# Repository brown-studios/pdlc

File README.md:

# PDLC driver

Drives [polymer dispersed liquid crystal (PDLC) film](https://en.wikipedia.org/wiki/Smart_glass#Polymer-dispersed_liquid-crystal_devices) from a 12 V DC nominal power supply.

PDLC film is opaque when turned off and becomes clear when turned on.  For example, you can apply it to a window to replace a privacy curtain or to create a diffuse surface for a projection screen on demand.

## Features

Here are some of the features of this PDLC driver board:

- Runs on a 12 V DC battery or power supply at a maximum of 16 V DC
- Drives approximately 4 square meters of PDLC film depending on its electrical characteristics with 15 W of power at 60 V AC peak-to-peak nominal
- Shuts off automatically to protect the battery when the supply voltage falls below 10.6 V DC and resumes operation at 11.5 V
- Includes several forms of circuit protection for the supply and the film
- Detach the terminal blocks from the device for easier wiring
- Optional external I/O functions
  - Connect the mode input to an external momentary push button or a normally open switch to control the state of the film from a convenient location
  - Connect the output enable control signal to a switch to control whether the PDLC film is operable (e.g. can be wired to a door sensor to prevent activation of the film when the door is opened)
  - Connect the auxiliary load output to control another device in tandem with the PDLC film, supports low-side switching of a 200 mA load at up to 20 V maximum (e.g. can be wired to an external indicator)
  - Connect an external I2C controller to control the driver programmatically
  - Connect your own accessories to the expansion port

Please refer to the [design and errata](./hardware/v2/design-and-errata.md) for technical details and schematics.

## Usage

If you have not yet [installed](#installation) and [setup](#setup) the device, do that first then proceed with usage.

How you use the PDLC driver depends on how you have configured it and integrated it with other systems.

By default, the PDLC film toggles on and off when you press the `MODE` button on the device.  When the film is on, it will turn clear, and when it is off, it will become diffuse and provide privacy.  The transition usually happens in less than a second but the film may take longer to change depending on your configuration settings or when the window is very cold.

You can connect an external push button or switch to change the state of the film from a more convenient location. If you have one, use that actuator instead of the `MODE` button.

As a safety feature, the film will not turn on unless the output enable control signal is active, so you may also need to perform another action to enable the film (such as closing the door if you have connected the output enable to a door switch).

You can connect an auxiliary load to the PDLC driver and configure it such that it turns on or off based on the state of the PDLC film automatically. So turning on or off the PDLC film can have additional effects depending on how you have wired things up.

Also, you can programmatically control the PDLC driver using I2C and adjust many internal settings and use advanced functionality such as dimming.  You'll need to write code for this or use an integration that someone else has made.

The `POWER` indicator illuminates for 10 seconds after you supply power to the device then turns off.

The `STATUS` indicator color indicates the status of the PDLC driver during normal operation.  The indicator may blink a certain number of times, pause, then repeat to encode information about a problem.  This table explains the significance of the patterns.

| Status color | Pattern    | Meaning |
| ------------ | ---------- | ------- |
| GREEN        | steady     | The PDLC driver is providing power to the PDLC film. |
| YELLOW       | steady     | The PDLC driver is turning on and verifying its operation. |
| AMBER        | 1 blink    | The PDLC driver was commanded to turn the film on but the output enable control signal is inactive so the driver is not providing power to the PDLC film. |
| RED          | 1 blinks   | HV_TIMEOUT: Boost converter did not report power good within the expected time after being enabled. |
| RED          | 2 blinks   | HV_FAULT: Boost converter reported power good then subsequently reported not power good. |
| RED          | 3 blinks   | OUTPUT_TIMEOUT: Buck converter did not report power good within the expected time after being enabled. |
| RED          | 4 blinks   | OUTPUT_FAULT: Buck converter reported power good then subsequently reported not power good. |
| RED          | 5 blinks   | DRIVER: An error occurred in the driver. |

Refer to the [setup](#setup) guide for information about how this indicator is used while configuring settings.

## Troubleshooting

When the PDLC film doesn't turn on when you think it should...

- Try turning the film off then on again and look at the `STATUS` indicator for clues.  Perhaps the output is not enabled.
- Disconnect and reconnect power to the device.  The `POWER` indicator should illuminate briefly once power is connected.
- Ensure that your power supply or battery is supplying at least 11.5 V to the device.
- Check that the settings are compatible with your installation.
- If under programmatic control, disconnect the external I2C controller, factory reset the settings, and try again using the built-in buttons to confirm basic operation.
- Check all wiring connections, fuses, and external control inputs.

When the PDLC film doesn't turn off when you think it should...

- Check that the settings are compatible with your installation.
- Check all wiring connections, fuses, and external control inputs.

## Setup

If you have not yet [installed](#installation) the device, do that first then proceed with setup.

Start by locating the `MODE` button, `SET` button, and `STATUS` indicator on the PDLC driver [as shown during installation](#installation).  Here's how to navigate the setting menus.

1. If you have connected an external switch to the `CONTROL CTRL_MODE_IN` terminal, then turn the switch off before changing settings to prevent interference with the `MODE` push button of the PDLC driver.
2. Press the `SET` button to turn off the PDLC film and enter the first setting menu.
3. Look at the `STATUS` indicator.
  - The color of the status indicator tells you which setting menu is active.
  - The indicator will blink a certain number of times, pause, then repeat.  The number of blinks tells you which option of the setting menu is selected.
4. Press the `MODE` button to advance to the next option.  The indicator will begin blinking a different number of times corresponding to the newly selected option.
5. Press the `SET` button to advance to the next setting menu and the color of the `STATUS` indicator will change.  Repeat from step 3 to continue changing settings.
6. Once you have configured the last option, the `STATUS` indicator will turn off and return to normal function.  Similarly, if you wait 30 seconds without interacting with the setting menu the device will exit the setting menu automatically.

> ![IMPORTANT]
> To reset the device to factory default settings, press and hold the `SET` button for 10 seconds until the indicator cycles through a rainbow pattern to confirm.

| Menu color | Option blinks  | Behavior |
| ---------- | -------------- | -------- |
| BLUE       | 1 (default)    | The PDLC film toggles on and off each time `MODE` is pressed. Use this option when you connect a momentary push button to the `CONTROL CTRL_MODE_IN` terminal. |
| BLUE       | 2              | The PDLC film turns on while `MODE` is pressed and turns off while `MODE` is released. Use this option when you connect a normally open switch to the `CONTROL CTRL_MODE_IN` terminal. |
| BLUE       | 3              | The PDLC film state is always on whenever the output enable control signal is active. Use this option when you are controlling the PDLC driver programmatically and do not want the `MODE` button to interfere. |
| BLUE       | 4              | The PDLC film state is always off. Use this option when you are controlling the PDLC driver programmatically and do not want the `MODE` button to interfere. |
| MAGENTA    | 1 (default)    | The PDLC film transitions from opaque to clear as quickly as possible. |
| MAGENTA    | 2              | The PDLC film transitions from opaque to clear gradually over a duration of about 0.5 seconds. |
| MAGENTA    | 3              | The PDLC film transitions from opaque to clear gradually over a duration of about 1 second. |
| MAGENTA    | 4              | The PDLC film transitions from opaque to clear gradually over a duration of about 2 seconds. |
| CYAN       | 1 (default)    | The auxiliary load output turns on when the PDLC film is on and turns off otherwise (same state). |
| CYAN       | 2              | The auxiliary load output turns off when the PDLC film is on and turns on otherwise (opposite state). |
| CYAN       | 3              | The auxiliary load output is always on. |
| CYAN       | 4              | The auxiliary load output is always off. |

## Installation

To begin installing and using your PDLC driver, locate these parts of your device:

| Part                     | Function |
| ------------------------ | -------- |
| `POWER` terminal block   | Connect the power supply and the PDLC film as described in the [wiring guide](#wiring). |
| `CONTROL` terminal block | Connect the control inputs and outputs as described in the [wiring guide](#wiring). |
| `POWER` indicator        | Indicates that the device has power.  Turns off automatically after a few seconds of inactivity. |
| `STATUS` indicator       | Indicates the status of the device and provides visual feedback while you configure settings. |
| `MODE` button            | By default, toggles the PDLC panel on/off.  Can be configured to behave in other ways. |
| `SET` button             | Configures device settings. |
| `EN` solder jumper       | Solder closed to force the output enable control signal to be always active. |
| `EXT I2C` connector      | Allows an external device to control the PDLC driver programmatically using a [QWIIC-compatible](https://www.sparkfun.com/qwiic) I2C interface with galvanic isolation. Additional I2C devices can also be connected in a daisy-chain. |
| `EXPANSION` header       | Connect your own accessories to this port to take advantage of otherwise unused microcontroller pins. |

### Identify the terminals

Remove both terminal blocks from the device by grasping the sides of a block and gently pulling the block out from its socket.  Do not tug on any wires that you may have already connected to the terminal blocks because pulling on the wires could damage them.

Identify the terminals of each terminal block.  You may use the silkscreen legend on the back side of the PCB as a guide, taking care to note the orientation of the connector when it is plugged in.  The following sections will describe these connections in more detail.

We recommend crimping [electric wire ferrules](https://en.wikipedia.org/wiki/Electric_wire_ferrule) onto the wires before screwing them into place to make your connections more secure.  Only moderate screw tension is required.

| Block    | Terminal | Name         | Function |
| -------- | -------- | ------------ | -------- |
| POWER    | 1        | GND          | Power supply input with negative polarity. |
| POWER    | 2        | 12V_IN       | Power supply input with positive polarity. |
| POWER    | 3        | PDLC_OUT_A   | PDLC panel AC output A. |
| POWER    | 4        | PDLC_OUT_B   | PDLC panel AC output B. |
| CONTROL  | 1        | GND          | Connected to `POWER GND`. |
| CONTROL  | 2        | CTRL_EN_IN   | Output enable switch input.  Active when connected to `GND`. |
| CONTROL  | 3        | CTRL_MODE_IN | Mode switch input.  Active when connected to `GND`. |
| CONTROL  | 4        | GND          | Connected to `POWER GND`. |
| CONTROL  | 5        | LOAD_OUT     | Auxiliary load output. |
| CONTROL  | 6        | 12V_OUT      | Connected to the 12V rail downstream of the internal fuse circuit protection.  DO NOT CONNECT TO POWER SUPPLY. |

### Connect the power supply (required)

You must connect the driver to a suitable 12 V DC nominal power supply.  It must be capable of supplying at least 2 amps of current and have suitable overcurrent protection such as a fuse or circuit breaker.

Use 20 AWG (0.5 mm^2) wire or larger to make the connections.

Connect the `POWER GND` terminal to the negative (ground) side of your power supply.

Connect the `POWER 12V_IN` terminal to a 3 A fuse or circuit breaker attached to the positive side of your power supply.

### Connect the PDLC film (required)

Use 22 AWG (0.3 mm^2) wire or larger to make the connections, preferably double-insulated.

Connect the `POWER PDLC_OUT_A` and `POWER PDLC_OUT_B` terminals to the PDLC film.  Either terminal can be connected to the PDLC film in either orientation because the film uses AC and there is no distinct polarity.

> ![WARNING]
> The PDLC power wires carry high voltage similar to domestic electrical wiring systems.  They can deliver a small electric shock that could be harmful to people so please ensure that these wires are adequately insulated and without exposed connections that could accidentally be touched!
>
> If the connection passes through a contact surface that might intermittently be exposed to people or to the environment (such as through a sliding door contact plate) install a safety device to deactivate the output enable control signal (such as a door switch) when those contacts may be exposed to reduce the risk of harm.

### Connect the output enable control signal (required)

The PDLC driver only provides power to the PDLC film when the output enable control signal is connected to ground.  This mechanism can be used to implement safety features to automatically disable the film when it is not safe to operate (such as when the contacts may be exposed as described in the previous section) or to remotely enable or disable the film using other devices.

> ![IMPORTANT]
> By default, the output enable control signal is not connected to anything (it is inactive) and the driver will not operate the PDLC film.  So for the PDLC film to operate, you must make a connection to activate the output enable control signal.

Here are three ways to do activate the output enable control signal:

- Connect a switch between the `CONTROL CTRL_EN_IN` and `CONTROL GND` terminals that is closed whenever it is safe to operate the PDLC film and open otherwise.  Alternatively, you may use a relay, transistor, or an optocoupler to drive the signal low (connect it to ground).
- Connect a short piece of wire with bare ends between the `CONTROL CTRL_EN_IN` and `CONTROL GND` terminals to ensure that the signal is always active when there is no reason to disable the film.
- Solder the `EN` jumper closed to bypass the `CONTROL` terminal block and ensure that the signal is always active when there is no reason to disable the film.

### Connect an external mode actuator (optional)

Optionally, you can connect an external actuator to control the mode of the PDLC driver from a more convenient location such as when you install the PDLC driver inside of a cabinet.

Choose one of following actuators and make note of its corresponding `MODE` behavior.

| Actuator type              | Behavior | Description |
| -------------------------- | -------- | ----------- |
| SPST momentary push button | Toggle   | Toggle the film on or off each time the button is pressed. |
| SPST normally open switch  | On / Off | Turn the film on when the switch is closed and off when the switch is open. |

Use 24 AWG (0.2 mm^2) wire or larger to make the connections.

Connect the actuator to the `CONTROL CTRL_MODE_IN` and `CONTROL GND` terminals such that the circuit is closed when the button is pressed or the switch is in the on position.

In place of a button or switch, you may use different actuators that perform a similar electric function, such as a relay, transistor, or optocoupler to drive the signal low (connect it to ground).  And you may also connect multiple push button actuators in parallel to toggle the mode from several locations.

Later during [setup](#setup) you must set the mode button behavior for the type of actuator that you selected.

### Connect an auxiliary load (optional)

Optionally, you can connect an auxiliary load that will receive power when the PDLC film is either on or off according to the settings.  You can use this output to power an external indicator, relay, optocoupler, or other small load that can switch on and off based on the PDLC film state.

Use 24 AWG (0.2 mm^2) wire or larger to make the connections.

Connect the `CONTROL LOAD_OUT` terminal to the negative terminal of the load.

Connect the load's positive terminal to the load's power supply, preferably with adequate current limiting or a small fuse to stay within the rating of the load output.  The load's power supply must share a common ground with `CONTROL GND`.

> ![IMPORTANT]
> The auxiliary output is a low-side solid state switch (MOSFET).  When active, the `CONTROL LOAD_OUT` terminal behaves as if it has been shorted to `CONTROL GND` which completes the circuit to power the load.  The load output is rated for drive 200 mA at up to 20 V maximum.  Please pay attention to the current requirements of the load to avoid exceeding the rating and damaging your devices.

### Connect an external I2C controller (optional)

Optionally, you can connect the PDLC driver to an external I2C controller.

Connect the controller to either port labeled `EXT I2C` using a standard 4-pin QWIIC bus JST SH connector.  You may also connect additional devices downstream using the other port to form a daisy-chain.

The circuit board has an [ISO1640](https://www.ti.com/lit/ds/symlink/iso1640.pdf) to galvanically isolate the PDLC driver from the I2C port.  Here's what that means:

- The devices can be powered on and off independently (hot-plugging).
- The devices do not need to be connected to the same ground so they can be powered from different supplies and they will not form ground loops when connected.  The isolation barrier is rated for at least 450 Vrms which is suitable for many automotive applications where devices are nominally connected to the same chassis ground but there may be a small voltage difference between nodes.
- The PDLC driver's `EXT I2C` port is protected from ESD (electrostatic discharges).

(TODO: Link to the I2C target protocol)

### Plug the terminal blocks into the device (required)

Now that you have made all of the wiring connections, turn off or disconnect the power supply, gently plug the terminal block in until they are fully seated, then turn on or reconnect the power supply.

Congratulations!  Now you're ready to setup the device configuration (if you need to change the defaults).

## Electrical information

### Recommended operational parameters and circuit protection

Supply:

- Voltage: 12 V DC nominal and absolute maximum range from 10 to 16 V DC
- Wiring: minimum 20 AWG (0.5 mm²)
- Circuit protection
  - Internal: built-in 2 A polyfuse, transient voltage suppressor, reverse polarity protection, and under voltage lock-out below 10.6 V
  - External: add a 3 A fuse or circuit breaker to protect the wiring to the device

Load:

- Voltage: 60 V AC nominal at 100 Hz
- Current: 300 mA maximum continous load
- Power output: 15 W maximum continuous load
- Circuit protection
  - Internal: built-in overload, over voltage, and over temperature protection
  - External: ensure wires are adequately insulated and not exposed to touch

In case of an overload such as exceeding the maximum output current or a short circuit, the power supply will hiccup until the overload condition is removed.

Please test your set up carefully if you choose to operate the PDLC driver beyond these recommendations.

### PDLC film electrical characteristics

Here is some general information about the electrical characteristics of PDLC films for which this driver was design.  If your PDLC film has significantly different electrical characteristics, please follow the tuning instructions or contact the author for advice on using this driver with your film.

The film's capacitance is proportional to its surface area, around 10 uF per square meter.  It becomes clear when charged and opaque when discharged.

The film's resistance is inversely proportional to its surface area, generally in the tens to hundreds of kiloohms.  It self-discharges rapidly and becomes opaque when power is removed.

The film's clarity increases with voltage.  It is opaque at 0 V, begins to clear around 20 to 30 V, is nearly transparent around 50 V, and becomes slightly clearer with increasing voltage.

The film must be driven with AC to produce an alternating electric field to orient the liquid crystals and it may be damaged when driven in one polarity for too long.  At very low frequencies, the film acts as a shutter.  As the frequency rises to a few hertz, the film will appear to pulse between opaque and clear states.  At higher frequencies, the film appears clear.  Mains AC frequencies (50 / 60 Hz) seem adequate.

### PDLC film data

Here's some information about PDLC films that the driver has been tested with.  

- FilmBase PDLC self-adhesive grey film
  - Operating voltage: 60 V AC (manufacturer recommendation)
  - Frequency: 50/60 Hz (manufacturer recommendation)
  - Power: < 5W / m^2 (manufacturer claim)
  - Capacitance: ~12 uF / m^2 (measured)

## How to build the firmware

The firmware is based on Zephyr RTOS v4.3 and compiled with `west`.

1. Install the Zephyr RTOS SDK tools.  You can either follow the [Zephyr Getting Started Guide](https://docs.zephyrproject.org/latest/develop/getting_started/index.html) or install an extension for your IDE, such as [Zephyr IDE](https://zephyr-ide.mylonics.com/) or [Workbench for Zephyr](https://z-workbench.com/), that can install the tools for you.

2. Install the [xPack OpenOCD](https://xpack-dev-tools.github.io/openocd-xpack/docs/install/) package for your OS and add it to your system `PATH`.  This step is needed because the version of OpenOCD that is distributed with Zephyr is too old.  We need OpenOCD v0.12.0-7 at minimum.

3. Get the code and its dependencies.  This is a little more complicated than simply cloning this git repository because the Zephyr `west` multi-tool assumes that all of the code resides within a top directory called a workspace.  You will need to create an empty directory to be the workspace first.  Here's how to do it from the command-line and the same thing can be done with IDE extensions.

```sh
$ mkdir pdlc-workspace
$ cd pdlc-workspace
$ west init -m https://github.com/brown-studios/pdlc
$ west update
```

4. Build and the firmware (either release or debug).

```sh
$ cd pdlc/firmware/app
$ west build -p -d build/release
$ west build -p -d build/debug -- -DFEATURE_LOG=y -DFEATURE_DEBUG=y
```

5. Connect an ST-Link v3 programmer to the `DEBUG` port with an `STDC14` cable.  Flash the firmware.

```sh
$ cd pdlc/firmware/app
$ west flash
```

## Design history

v2.0: Second prototype.  Uses a microcontroller to generate commutation waveforms in software and more careful circuitry to limit the output current.  Should work with larger panels and be safer to operate.  Can be controlled with two switch inputs and interface with a host device as an I2C target.

v1.0: Initial prototype.  Uses a 555 timer and inverter to generate commutation waveforms.  Works fine for small PDLC samples.  Can't drive larger panels without modification because it does not wait for the power-good signal to be asserted before energizing the panel and it does not limit the current so it hiccups.  During testing, the board was modified to replace the timer with a microcontroller to generate PWM signals in open loop control which helped it drive larger panels but it still could not achieve the expected output power.

## Notice

The PDLC driver software, documentation, design, and all copyright protected artifacts are released under the terms of the [MIT license](LICENSE).

The PDLC driver hardware is released under the terms of the [CERN-OHL-W license](hardware/LICENSE).

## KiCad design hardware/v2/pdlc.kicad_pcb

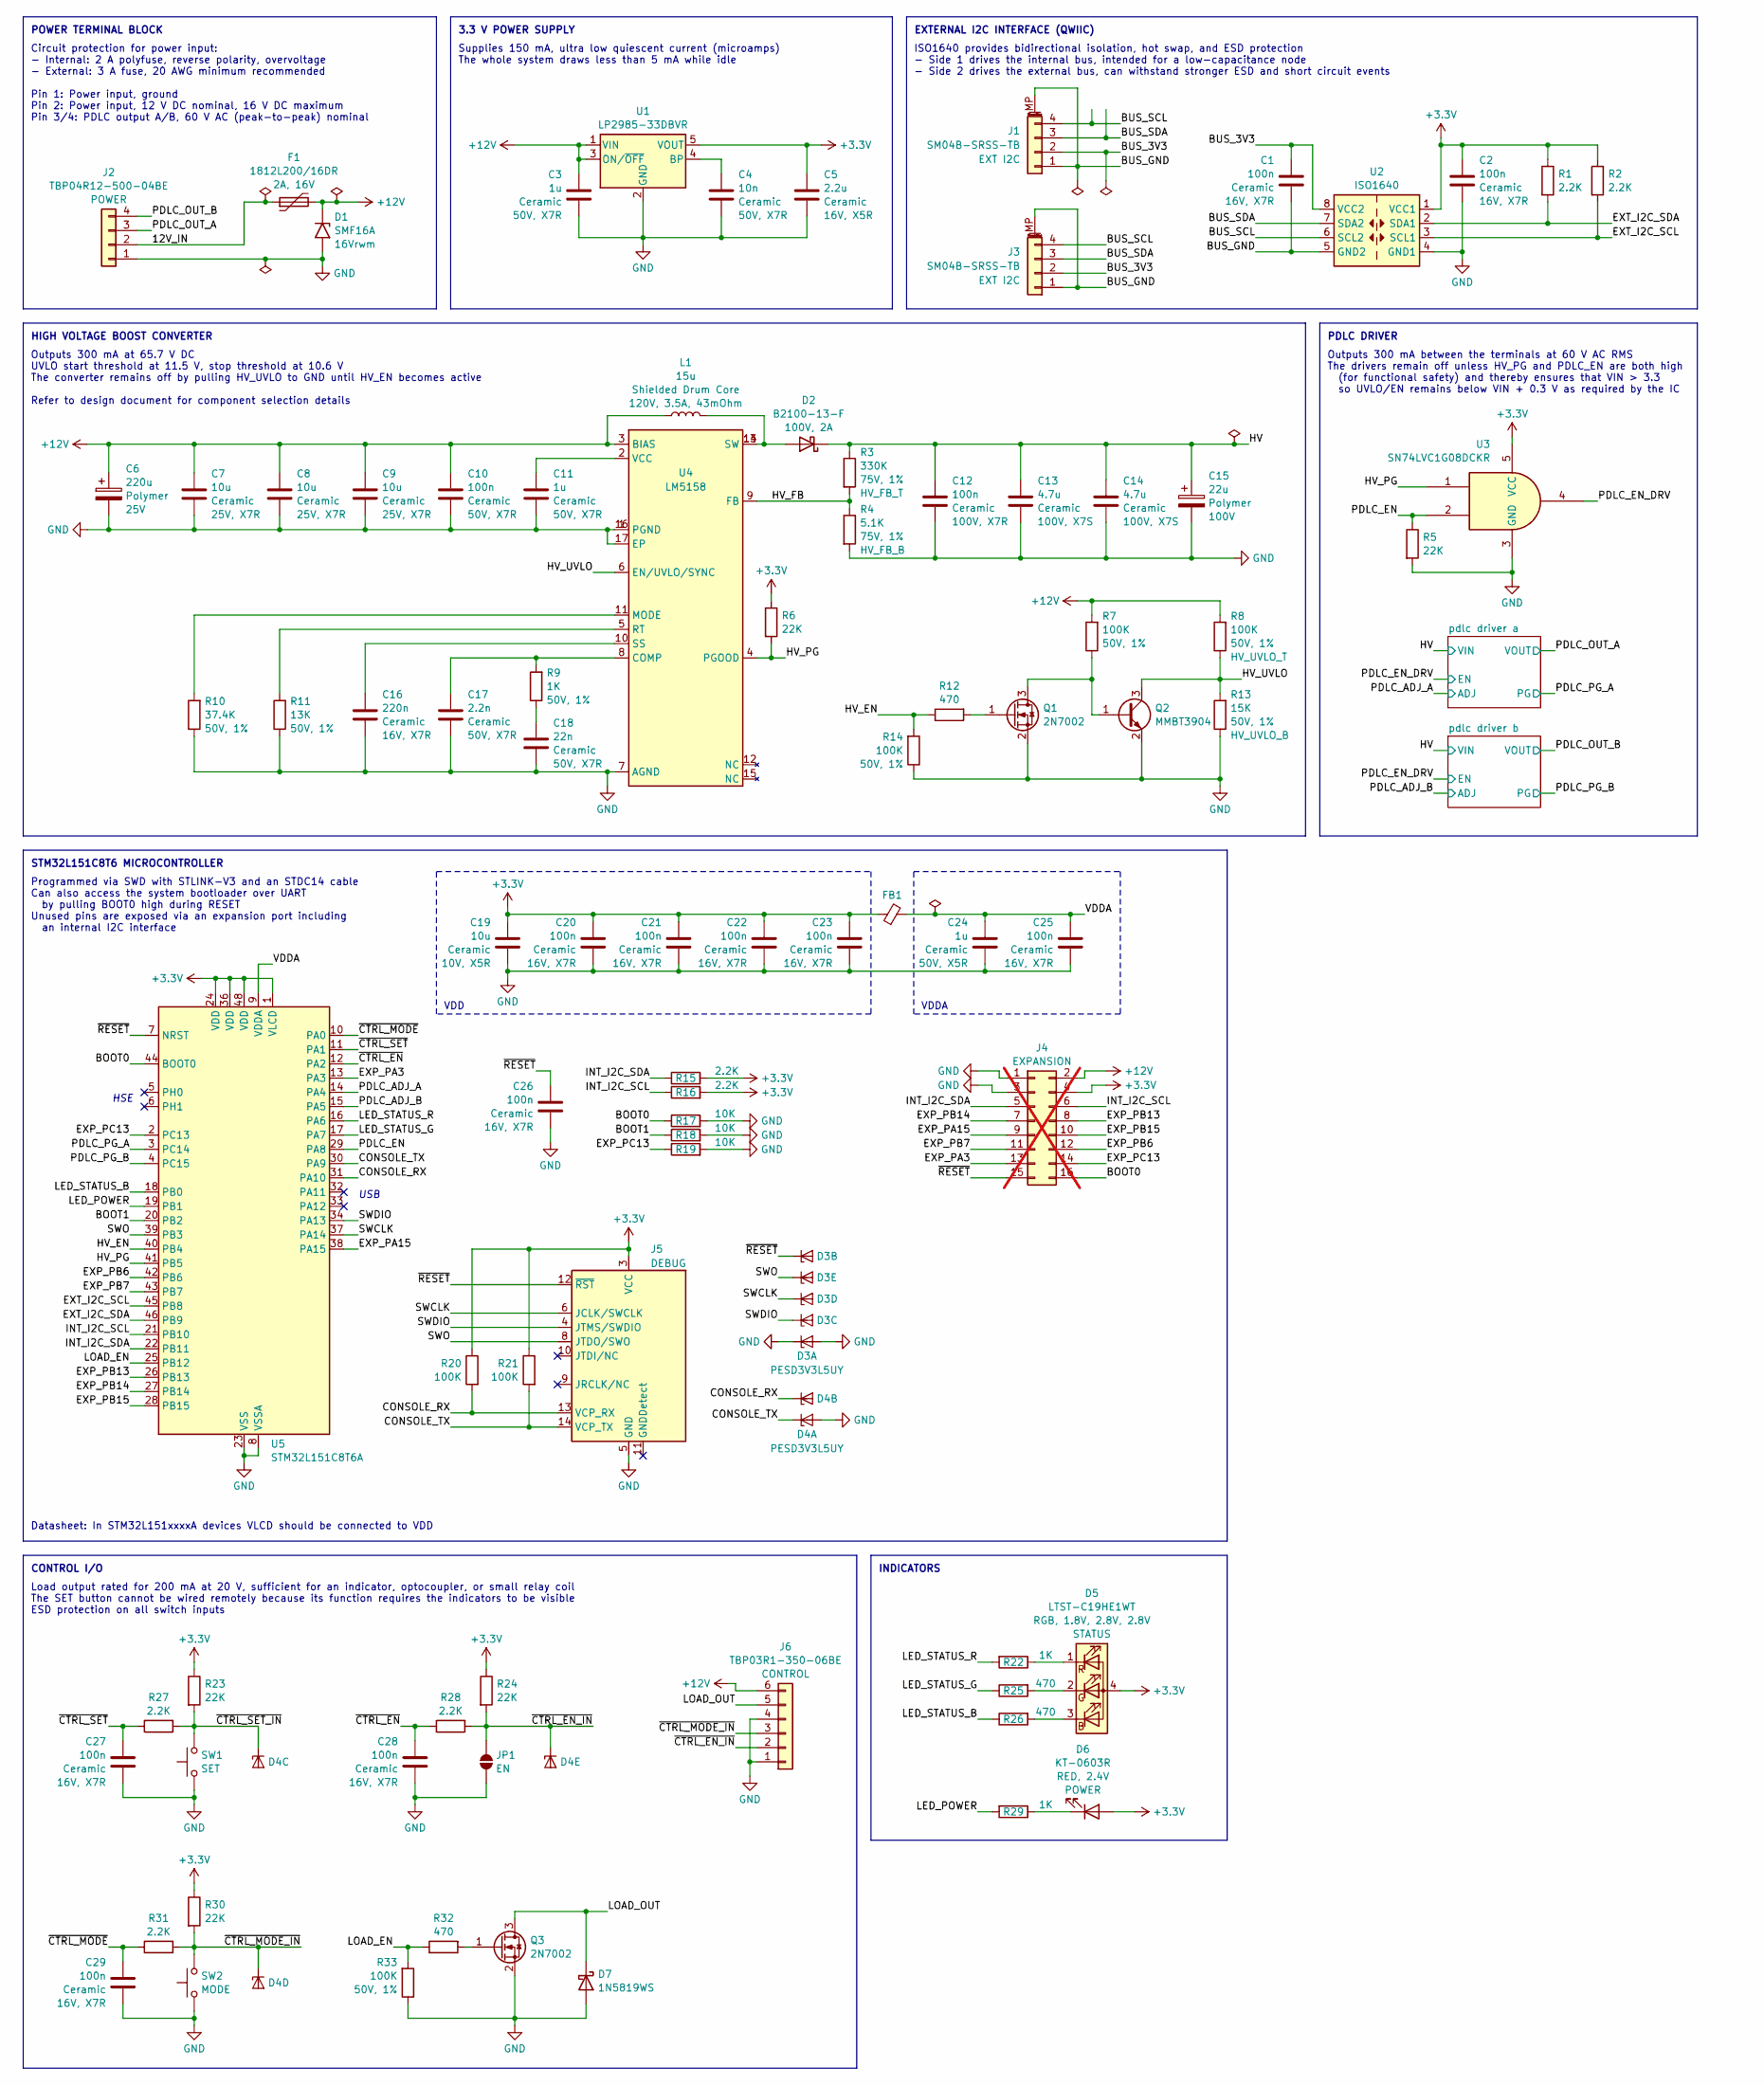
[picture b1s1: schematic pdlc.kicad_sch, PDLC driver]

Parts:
C1, C2, C20, C21, C22, C23, C25, C26, C27, C28, C29: 100n; C_0402_1005Metric; Rating 16V, X7R; LCSC C1525
C3, C11: 1u; C_0805_2012Metric; Rating 50V, X7R; LCSC C28323
C4: 10n; C_0402_1005Metric; Rating 50V, X7R; LCSC C15195
C5: 2.2u; C_0603_1608Metric; Rating 16V, X5R; LCSC C23630
C6: 220u; CP_Radial_D6.3mm_P2.50mm; Rating 25V; Part 2210250609R00; LCSC C2887216
C7, C8, C9: 10u; C_1210_3225Metric; Rating 25V, X7R; Part CL32B106KAJNNNE; LCSC C39232
C10: 100n; C_0603_1608Metric; Rating 50V, X7R; LCSC C14663
C12: 100n; C_1206_3216Metric; Rating 100V, X7R; Part CL31B104KCFNNNE; LCSC C1945
C13, C14: 4.7u; C_1210_3225Metric; Rating 100V, X7S; Part HMK325C7475KN-TE; LCSC C697607
C15: 22u; CP_Elec_6.3x9.9; Rating 100V; Part 2201010609TR; LCSC C19270543
C16: 220n; C_0402_1005Metric; Rating 16V, X7R; LCSC C16772
C17: 2.2n; C_0603_1608Metric; Rating 50V, X7R; LCSC C1604
C18: 22n; C_0402_1005Metric; Rating 50V, X7R; LCSC C1532
C19: 10u; C_0603_1608Metric; Rating 10V, X5R; LCSC C19702
C24: 1u; C_0603_1608Metric; Rating 50V, X5R; LCSC C15849
D1: SMF16A; D_SMF; Rating 16Vrwm; Part Alternative SMF16A-E3-08; LCSC C207257
D2: B2100-13-F; D_SMB; Rating 100V, 2A; LCSC C110479
D3, D4: PESD3V3L5UY; SOT-363_SC-70-6; LCSC C3021133
D5: LTST-C19HE1WT; LED_LiteOn_LTST-C19HE1WT; Rating RGB, 1.8V, 2.8V, 2.8V
D6: KT-0603R; LED_0603_1608Metric; Rating RED, 2.4V; LCSC C2286
D7: 1N5819WS; D_SOD-323; LCSC C191023
F1: 1812L200/16DR; 1812L; Rating 2A, 16V; LCSC C439873
FB1: 450mOhm; L_0603_1608Metric; Rating 600ohm@100Mhz, 200mA; Part GZ1608D601TF; LCSC C1002
J1, J3: SM04B-SRSS-TB; JST_SH_SM04B-SRSS-TB_1x04-1MP_P1.00mm_Horizontal; Part Alternative GT-A1002WRS-104SBT01; LCSC C160404
J2: TBP04R12-500-04BE; PhoenixContact_MSTBA_2,5_4-G_1x04_P5.00mm_Horizontal
J4: Conn_02x08_Odd_Even; PinSocket_2x08_P2.54mm_Vertical; not fitted
J5: Conn_ST_STDC14; SAMTEC_FTSH-107-01-L-DV-K-A; LCSC C5563894
J6: TBP03R1-350-06BE; PhoenixContact_MC_1,5_6-G-3.5_1x06_P3.50mm_Horizontal
JP1: SolderJumper_2_Open; SolderJumper-2_P1.3mm_Open_TrianglePad1.0x1.5mm
L1: 15u; WE-PD_1050P; Rating 120V, 3.5A, 43mOhm; Part 7447714150; LCSC C373521
Q1, Q3: 2N7002; SOT-23; LCSC C8545
Q2: MMBT3904; SOT-23; LCSC C20526
R1, R2, R15, R16, R27, R28, R31: 2.2K; R_0402_1005Metric; LCSC C25879
R3: 330K; R_0603_1608Metric; Rating 75V, 1%; LCSC C23137
R4: 5.1K; R_0603_1608Metric; Rating 75V, 1%; LCSC C23186
R5, R6, R23, R24, R30: 22K; R_0402_1005Metric; LCSC C25768
R7, R8, R14, R33: 100K; R_0402_1005Metric; Rating 50V, 1%; LCSC C25741
R9, R22, R29: 1K; R_0402_1005Metric; Rating 50V, 1%; LCSC C11702
R10: 37.4K; R_0402_1005Metric; Rating 50V, 1%; LCSC C25888
R11: 13K; R_0402_1005Metric; Rating 50V, 1%; LCSC C25754
R12, R25, R26, R32: 470; R_0402_1005Metric; LCSC C25117
R13: 15K; R_0402_1005Metric; Rating 50V, 1%; LCSC C25756
R17, R18, R19: 10K; R_0402_1005Metric; LCSC C25744
R20, R21: 100K; R_0402_1005Metric; LCSC C25741
SW1, SW2: SW_Push; SW_SPST_TS-1088-xR020; Part TS-1088-AR02016; LCSC C720477
U1: LP2985-33DBVR; SOT-23-5; LCSC C95414
U2: ISO1640; SOIC-8_3.9x4.9mm_P1.27mm; LCSC C5122339
U3: SN74LVC1G08DCKR; SOT-353_SC-70-5; LCSC C7832
U4: LM5158; LCSC C3188433
U5: STM32L151C8T6A; LQFP-48_7x7mm_P0.5mm; LCSC C95578

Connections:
+3.3V: C2.1, C5.2, C19.1, C20.1, C21.1, C22.1, C23.1, D5.4 (A), D6.2 (A), FB1.1, J4.4, J5.3 (VCC), R1.1, R2.1, R6.1, R15.2, R16.2, R20.1, R21.1, R23.1, R24.1, R30.1, U1.5 (VOUT), U2.1 (VCC1), U3.5 (VCC), U5.1 (VLCD), U5.24 (VDD), U5.36 (VDD), U5.48 (VDD); also elsewhere on the board
+12V: C3.1, C6.1, C7.1, C8.1, C9.1, C10.1, D1.1 (A1), F1.2, J4.2, J6.6, L1.2, R7.2, R8.2, U1.1 (VIN), U1.3 (ON/~OFF), U4.3 (BIAS)
/12V_IN: F1.1, J2.2
/BOOT0: J4.16, R17.1, U5.44 (BOOT0)
/BOOT1: R18.1, U5.20 (PB2)
/BUS_3V3: C1.1, J1.2, J3.2, U2.8 (VCC2)
/BUS_GND: C1.2, J1.1, J1.MP (MountPin), J3.1, J3.MP (MountPin), U2.5 (GND2)
/BUS_SCL: J1.4, J3.4, U2.6 (SCL2)
/BUS_SDA: J1.3, J3.3, U2.7 (SDA2)
/CONSOLE_RX: D4.3 (K2), J5.13 (VCP_RX), R20.2, U5.31 (PA10)
/CONSOLE_TX: D4.1 (K1), J5.14 (VCP_TX), R21.2, U5.30 (PA9)
/EXP_PA3: J4.13, U5.13 (PA3)
/EXP_PA15: J4.9, U5.38 (PA15)
/EXP_PB6: J4.12, U5.42 (PB6)
/EXP_PB7: J4.11, U5.43 (PB7)
/EXP_PB13: J4.8, U5.26 (PB13)
/EXP_PB14: J4.7, U5.27 (PB14)
/EXP_PB15: J4.10, U5.28 (PB15)
/EXP_PC13: J4.14, R19.1, U5.2 (PC13)
/EXT_I2C_SCL: R2.2, U2.3 (SCL1), U5.45 (PB8)
/EXT_I2C_SDA: R1.2, U2.2 (SDA1), U5.46 (PB9)
/HV: C12.1, C13.1, C14.1, C15.1, D2.1 (K), R3.1; also elsewhere on the board
/HV_EN: R12.1, R14.2, U5.40 (PB4)
/HV_FB: R3.2, R4.1, U4.9 (FB)
/HV_PG: R6.2, U3.1, U4.4 (PGOOD), U5.41 (PB5)
/HV_UVLO: Q2.3 (C), R8.1, R13.2, U4.6 (EN/UVLO/SYNC)
/INT_I2C_SCL: J4.6, R16.1, U5.21 (PB10)
/INT_I2C_SDA: J4.5, R15.1, U5.22 (PB11)
/LED_POWER: R29.2, U5.19 (PB1)
/LED_STATUS_B: R26.1, U5.18 (PB0)
/LED_STATUS_G: R25.1, U5.17 (PA7)
/LED_STATUS_R: R22.2, U5.16 (PA6)
/LOAD_EN: R32.1, R33.2, U5.25 (PB12)
/LOAD_OUT: D7.1 (K), J6.5, Q3.3 (D)
/PDLC_ADJ_A: U5.14 (PA4); also elsewhere on the board
/PDLC_ADJ_B: U5.15 (PA5); also elsewhere on the board
/PDLC_EN: R5.1, U3.2, U5.29 (PA8)
/PDLC_EN_DRV: U3.4; also elsewhere on the board
/PDLC_OUT_A: J2.3; also elsewhere on the board
/PDLC_OUT_B: J2.4; also elsewhere on the board
/PDLC_PG_A: U5.3 (PC14); also elsewhere on the board
/PDLC_PG_B: U5.4 (PC15); also elsewhere on the board
/SWCLK: D3.5 (K4), J5.6 (JCLK/SWCLK), U5.37 (PA14)
/SWDIO: D3.4 (K3), J5.4 (JTMS/SWDIO), U5.34 (PA13)
/SWO: D3.6 (K5), J5.8 (JTDO/SWO), U5.39 (PB3)
/VDDA: C24.1, C25.1, FB1.2, U5.9 (VDDA)
/~CTRL_EN_IN: D4.6 (K5), J6.2, JP1.2 (B), R24.2, R28.2
/~CTRL_EN: C28.1, R28.1, U5.12 (PA2)
/~CTRL_MODE_IN: D4.5 (K4), J6.3, R30.2, R31.2, SW2.2
/~CTRL_MODE: C29.1, R31.1, U5.10 (PA0)
/~CTRL_SET_IN: D4.4 (K3), R23.2, R27.2, SW1.2
/~CTRL_SET: C27.1, R27.1, U5.11 (PA1)
/~RESET: C26.1, D3.3 (K2), J4.15, J5.12 (~RST), U5.7 (NRST)
GND: C2.2, C3.2, C4.1, C5.1, C6.2, C7.2, C8.2, C9.2, C10.2, C11.2, C12.2, C13.2, C14.2, C15.2, C16.2, C17.2, C18.2, C19.2, C20.2, C21.2, C22.2, C23.2, C24.2, C25.2, C26.2, C27.2, C28.2, C29.2, D1.2 (A2), D3.1 (K1), D3.2 (A), D4.2 (A), D7.2 (A), J2.1, J4.1, J4.3, J5.5 (GND), J5.7 (GND), J6.1, J6.4, JP1.1 (A), Q1.2 (S), Q2.2 (E), Q3.2 (S), R4.2, R5.2, R10.1, R11.1, R13.1, R14.1, R17.2, R18.2, R19.2, R33.1, SW1.1, SW2.1, U1.2 (GND), U2.4 (GND1), U3.3 (GND), U4.1 (PGND), U4.7 (AGND), U4.16 (PGND), U4.17 (EP), U5.8 (VSSA), U5.23 (VSS), U5.35 (VSS), U5.47 (VSS); also elsewhere on the board
unnamed: C18.1, R9.1
unnamed: D2.2 (A), L1.1, U4.13 (SW), U4.14 (SW)
unnamed: D5.3 (BK), R26.2
unnamed: D5.2 (GK), R25.2
unnamed: D5.1 (RK), R22.1
unnamed: D6.1 (K), R29.1
unnamed: Q1.3 (D), Q2.1 (B), R7.1
unnamed: Q1.1 (G), R12.2
unnamed: Q3.1 (G), R32.2
unnamed: C4.2, U1.4 (BP)
unnamed: C17.1, R9.2, U4.8 (COMP)
unnamed: R10.2, U4.11 (MODE)
unnamed: R11.2, U4.5 (RT)
unnamed: C16.1, U4.10 (SS)
unnamed: C11.1, U4.2 (VCC)

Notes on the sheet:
STM32L151C8T6 MICROCONTROLLER
USB
Load output rated for 200 mA at 20 V, sufficient for an indicator, optocoupler, or small relay coil The SET button cannot be wired remotely because its function requires the indicators to be visible ESD protection on all switch inputs
HSE
Outputs 300 mA at 65.7 V DC UVLO start threshold at 11.5 V, stop threshold at 10.6 V The converter remains off by pulling HV_UVLO to GND until HV_EN becomes active Refer to design document for component selection details
VDDA
POWER TERMINAL BLOCK
ISO1640 provides bidirectional isolation, hot swap, and ESD protection - Side 1 drives the internal bus, intended for a low-capacitance node - Side 2 drives the external bus, can withstand stronger ESD and short circuit events
3.3 V POWER SUPPLY
Supplies 150 mA, ultra low quiescent current (microamps) The whole system draws less than 5 mA while idle
Circuit protection for power input: - Internal: 2 A polyfuse, reverse polarity, overvoltage - External: 3 A fuse, 20 AWG minimum recommended Pin 1: Power input, ground Pin 2: Power input, 12 V DC nominal, 16 V DC maximum Pin 3/4: PDLC output A/B, 60 V AC (peak-to-peak) nominal
Programmed via SWD with STLINK-V3 and an STDC14 cable Can also access the system bootloader over UART by pulling BOOT0 high during RESET Unused pins are exposed via an expansion port including an internal I2C interface
INDICATORS
Outputs 300 mA between the terminals at 60 V AC RMS The drivers remain off unless HV_PG and PDLC_EN are both high (for functional safety) and thereby ensures that VIN > 3.3 so UVLO/EN remains below VIN + 0.3 V as required by the IC
EXTERNAL I2C INTERFACE (QWIIC)
Datasheet: In STM32L151xxxxA devices VLCD should be connected to VDD
PDLC DRIVER
HIGH VOLTAGE BOOST CONVERTER
VDD
CONTROL I/O

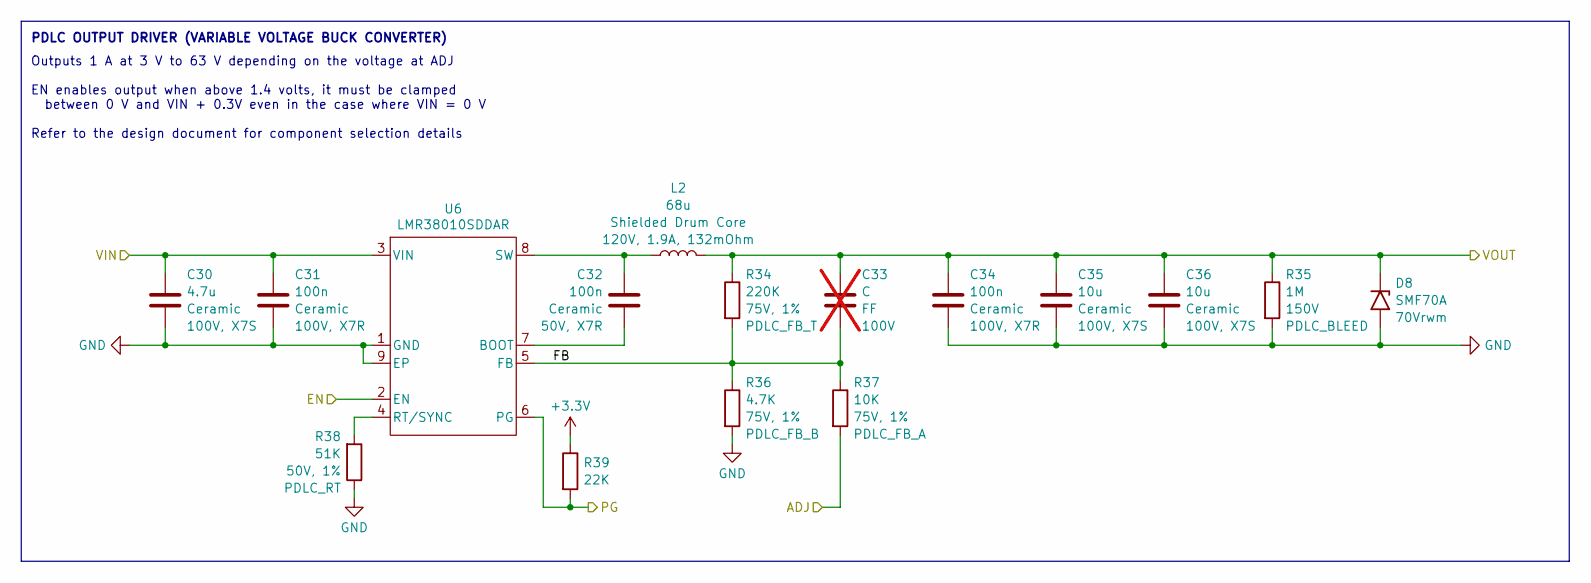
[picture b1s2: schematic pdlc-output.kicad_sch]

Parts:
C30: 4.7u; C_1210_3225Metric; Rating 100V, X7S; Part HMK325C7475KN-TE; LCSC C697607
C31, C34: 100n; C_1206_3216Metric; Rating 100V, X7R; Part CL31B104KCFNNNE; LCSC C1945
C32: 100n; C_0603_1608Metric; Rating 50V, X7R; LCSC C14663
C33: C; C_0603_1608Metric; Rating 100V; not fitted
C35, C36: 10u; C_1210_3225Metric; Rating 100V, X7S; Part GRM32EC72A106KE05L; LCSC C576517
D8: SMF70A; D_SMF; Rating 70Vrwm; LCSC C1976954
L2: 68u; WE-PD_1050P; Rating 120V, 1.9A, 132mOhm; Part 7447714680; LCSC C5364067
R34: 220K; R_0603_1608Metric; Rating 75V, 1%; LCSC C22961
R35: 1M; R_0805_2012Metric; Rating 150V; LCSC C17514
R36: 4.7K; R_0603_1608Metric; Rating 75V, 1%; LCSC C23162
R37: 10K; R_0603_1608Metric; Rating 75V, 1%; LCSC C25804
R38: 51K; R_0402_1005Metric; Rating 50V, 1%; LCSC C25794
R39: 22K; R_0402_1005Metric; LCSC C25768
U6: LMR38010SDDAR; TI_SO-PowerPAD-8; LCSC C5219310

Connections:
+3.3V: R39.1; also elsewhere on the board
/HV: C30.1, C31.1, U6.3 (VIN); also elsewhere on the board
/PDLC_ADJ_A: R37.2; also elsewhere on the board
/PDLC_EN_DRV: U6.2 (EN); also elsewhere on the board
/PDLC_OUT_A: C33.1, C34.1, C35.1, C36.1, D8.1 (A1), L2.2, R34.1, R35.1; also elsewhere on the board
/PDLC_PG_A: R39.2, U6.6 (PG); also elsewhere on the board
/pdlc driver a/FB: C33.2, R34.2, R36.1, R37.1, U6.5 (FB)
GND: C30.2, C31.2, C34.2, C35.2, C36.2, D8.2 (A2), R35.2, R36.2, R38.1, U6.1 (GND), U6.9 (EP); also elsewhere on the board
unnamed: C32.2, U6.7 (BOOT)
unnamed: R38.2, U6.4 (RT/SYNC)
unnamed: C32.1, L2.1, U6.8 (SW)

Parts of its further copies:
C37: 4.7u; C_1210_3225Metric; Rating 100V, X7S; Part HMK325C7475KN-TE; LCSC C697607
C38, C41: 100n; C_1206_3216Metric; Rating 100V, X7R; Part CL31B104KCFNNNE; LCSC C1945
C39: 100n; C_0603_1608Metric; Rating 50V, X7R; LCSC C14663
C40: C; C_0603_1608Metric; Rating 100V; not fitted
C42, C43: 10u; C_1210_3225Metric; Rating 100V, X7S; Part GRM32EC72A106KE05L; LCSC C576517
D9: SMF70A; D_SMF; Rating 70Vrwm; LCSC C1976954
L3: 68u; WE-PD_1050P; Rating 120V, 1.9A, 132mOhm; Part 7447714680; LCSC C5364067
R40: 220K; R_0603_1608Metric; Rating 75V, 1%; LCSC C22961
R41: 1M; R_0805_2012Metric; Rating 150V; LCSC C17514
R42: 4.7K; R_0603_1608Metric; Rating 75V, 1%; LCSC C23162
R43: 10K; R_0603_1608Metric; Rating 75V, 1%; LCSC C25804
R44: 51K; R_0402_1005Metric; Rating 50V, 1%; LCSC C25794
R45: 22K; R_0402_1005Metric; LCSC C25768
U7: LMR38010SDDAR; TI_SO-PowerPAD-8; LCSC C5219310

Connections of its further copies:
+3.3V: R45.1; also elsewhere on the board
/HV: C37.1, C38.1, U7.3 (VIN); also elsewhere on the board
/PDLC_ADJ_B: R43.2; also elsewhere on the board
/PDLC_EN_DRV: U7.2 (EN); also elsewhere on the board
/PDLC_OUT_B: C40.1, C41.1, C42.1, C43.1, D9.1 (A1), L3.2, R40.1, R41.1; also elsewhere on the board
/PDLC_PG_B: R45.2, U7.6 (PG); also elsewhere on the board
/pdlc driver b/FB: C40.2, R40.2, R42.1, R43.1, U7.5 (FB)
GND: C37.2, C38.2, C41.2, C42.2, C43.2, D9.2 (A2), R41.2, R42.2, R44.1, U7.1 (GND), U7.9 (EP); also elsewhere on the board
unnamed: C39.2, U7.7 (BOOT)
unnamed: R44.2, U7.4 (RT/SYNC)
unnamed: C39.1, L3.1, U7.8 (SW)

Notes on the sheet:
Outputs 1 A at 3 V to 63 V depending on the voltage at ADJ EN enables output when above 1.4 volts, it must be clamped between 0 V and VIN + 0.3V even in the case where VIN = 0 V Refer to the design document for component selection details
PDLC OUTPUT DRIVER (VARIABLE VOLTAGE BUCK CONVERTER)

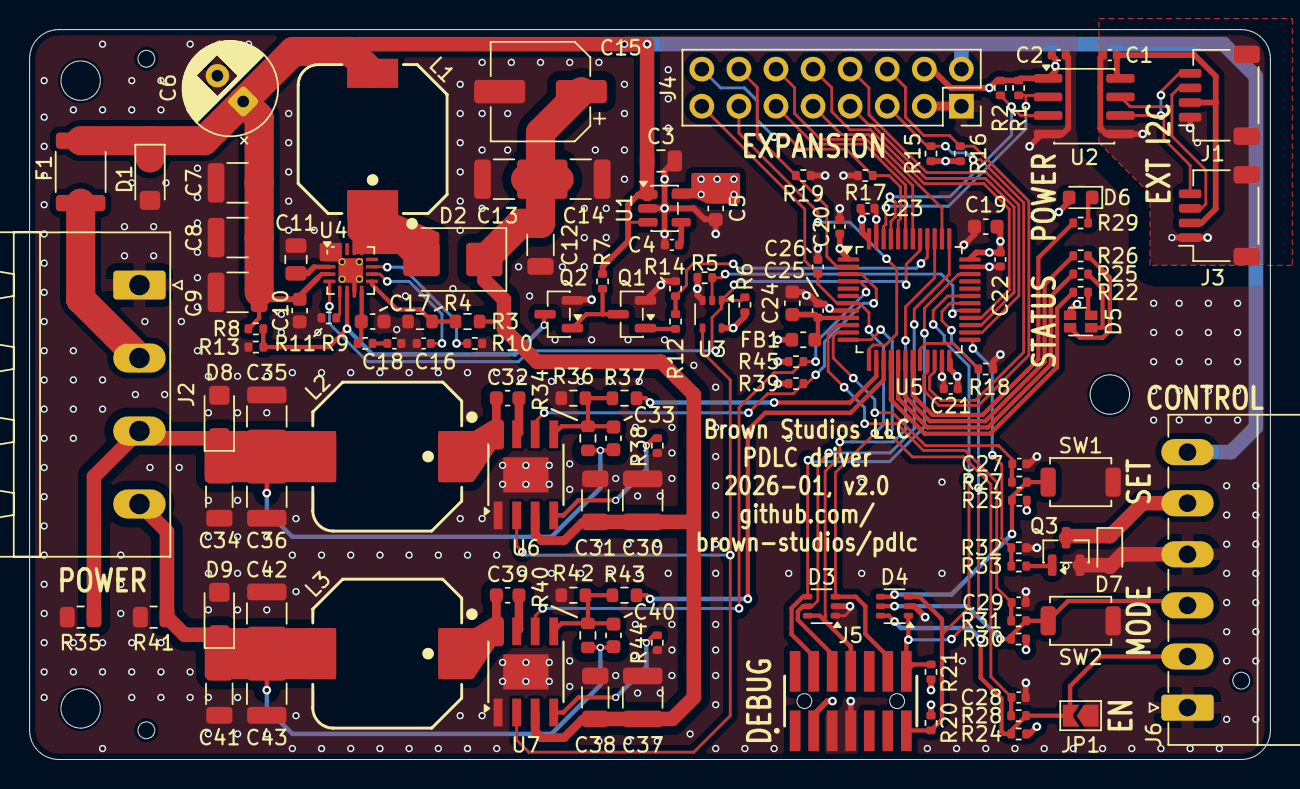
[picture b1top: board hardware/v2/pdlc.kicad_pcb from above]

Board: 4 copper layers, 85.0 x 50.0 mm, 127 parts (0 on the bottom side), 77 nets.

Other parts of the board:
MP1, MP1#2, MP1#3: MountingHole_2.7mm_M2.5
TH1, TH1#2, TH1#3: JLCPCB_PCBA_Tooling_Hole

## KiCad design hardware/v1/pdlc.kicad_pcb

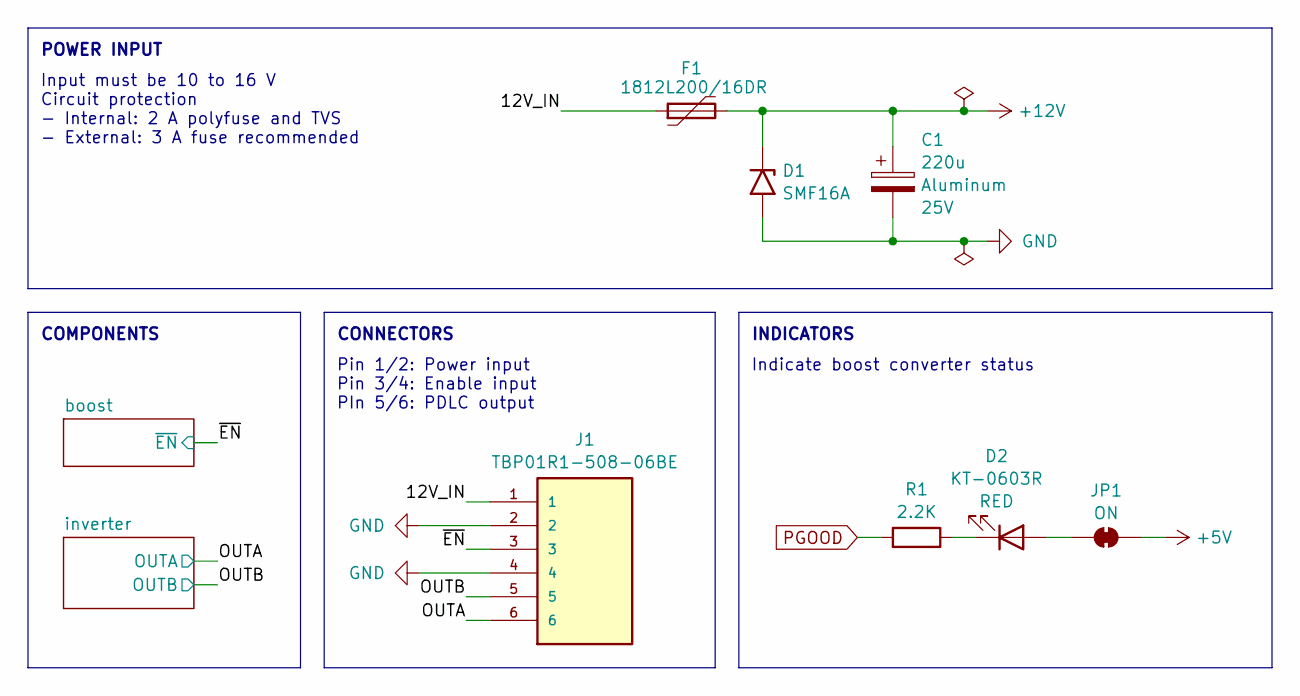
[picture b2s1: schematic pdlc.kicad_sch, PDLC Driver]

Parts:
C1: 220u; CP_Radial_D6.3mm_P2.50mm; Rating 25V; Part 2210250609R00; LCSC C2887216
D1: SMF16A; D_SMF; LCSC C207257
D2: KT-0603R; LED_0603_1608Metric_Pad1.05x0.95mm_HandSolder; Rating RED; LCSC C2286
F1: 1812L200/16DR; 1812L; LCSC C439873
J1: TBP01R1-508-06BE; CUI_TBP01R1-508-06BE
JP1: SolderJumper_2_Bridged; SolderJumper-2_P1.3mm_Bridged_RoundedPad1.0x1.5mm
R1: 2.2K; R_0603_1608Metric; LCSC C4190

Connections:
+5V: JP1.1 (A); also elsewhere on the board
+12V: C1.1, D1.1 (A1), F1.2; also elsewhere on the board
/12V_IN: F1.1, J1.1
/OUTA: J1.6; also elsewhere on the board
/OUTB: J1.5; also elsewhere on the board
/~EN: J1.3; also elsewhere on the board
GND: C1.2, D1.2 (A2), J1.2, J1.4; also elsewhere on the board
unnamed: D2.2 (A), JP1.2 (B)
unnamed: D2.1 (K), R1.1
PGOOD: R1.2; also elsewhere on the board

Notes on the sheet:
POWER INPUT
Indicate boost converter status
CONNECTORS
INDICATORS
COMPONENTS
Pin 1/2: Power input Pin 3/4: Enable input PIn 5/6: PDLC output
Input must be 10 to 16 V Circuit protection - Internal: 2 A polyfuse and TVS - External: 3 A fuse recommended

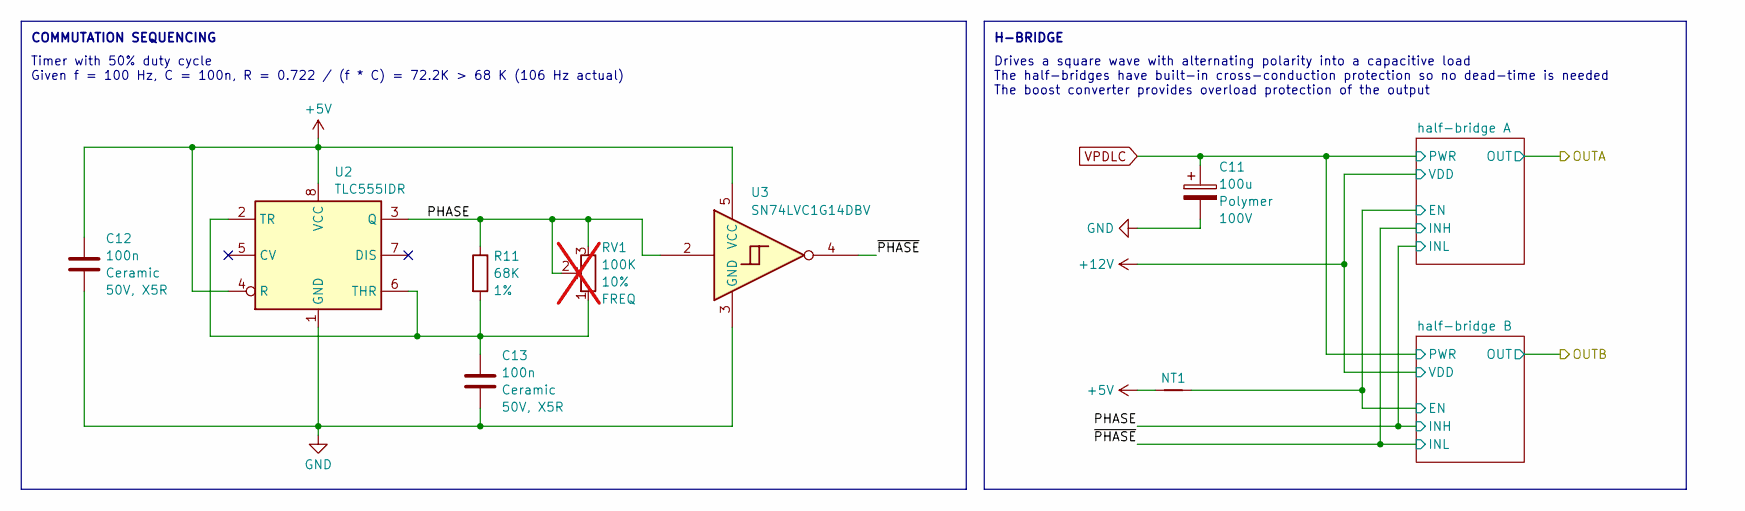
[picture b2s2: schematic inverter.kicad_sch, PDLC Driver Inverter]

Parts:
C11: 100u; CP_Radial_D10.0mm_P5.00mm; Rating 100V; Part 1011001013R00; LCSC C2887236
C12, C13: 100n; C_0603_1608Metric; Rating 50V, X5R; LCSC C14663
NT1: NetTie_2; NetTie-2_SMD_Pad0.2mm
R11: 68K; R_0603_1608Metric; Rating 1%; LCSC C23231
RV1: 100K; TRIM_3362P-1-502LF; Rating 10%; Part 3362P-1-104LF; not fitted
U2: TLC555IDR; SOIC-8_3.9x4.9mm_P1.27mm; LCSC C6987
U3: SN74LVC1G14DBV; SOT-23-5; LCSC C7835

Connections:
+5V: C12.1, NT1.1, U2.4 (R), U2.8 (VCC), U3.5 (VCC); also elsewhere on the board
/inverter/PHASE: R11.1, RV1.2, RV1.3, U2.3 (Q), U3.2; also elsewhere on the board
/inverter/half-bridge A/EN: NT1.2; also elsewhere on the board
/inverter/~PHASE: U3.4; also elsewhere on the board
GND: C11.2, C12.2, C13.2, U2.1 (GND), U3.3 (GND); also elsewhere on the board
unnamed: C13.1, R11.2, RV1.1, U2.2 (TR), U2.6 (THR)
VPDLC: C11.1; also elsewhere on the board

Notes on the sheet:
H-BRIDGE
Drives a square wave with alternating polarity into a capacitive load The half-bridges have built-in cross-conduction protection so no dead-time is needed The boost converter provides overload protection of the output
COMMUTATION SEQUENCING
Timer with 50% duty cycle Given f = 100 Hz, C = 100n, R = 0.722 / (f * C) = 72.2K > 68 K (106 Hz actual)

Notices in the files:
README.md:
The PDLC driver software, documentation, design, and all copyright protected artifacts are released under the terms of the [MIT license](LICENSE).
The PDLC driver hardware is released under the terms of the [CERN-OHL-W license](hardware/LICENSE).
